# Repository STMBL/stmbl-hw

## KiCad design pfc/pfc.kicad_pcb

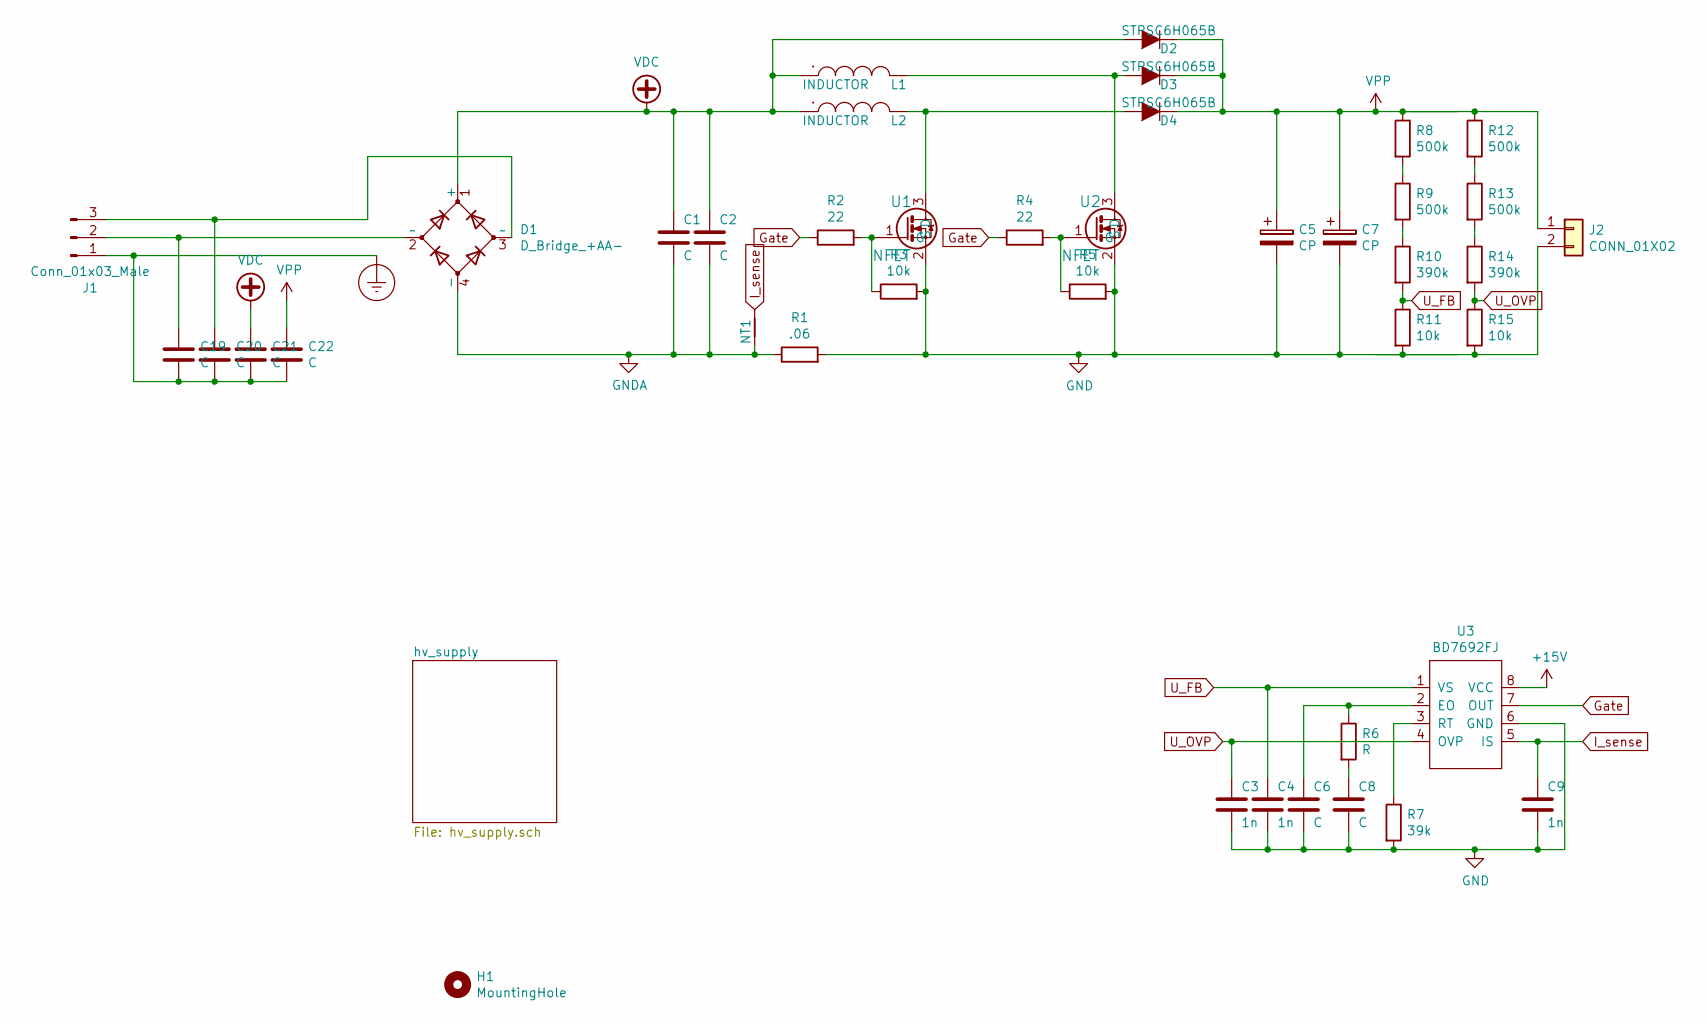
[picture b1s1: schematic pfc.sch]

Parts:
C1, C2: C; C_1812
C3, C4, C9: 1n; C_0603
C5, C7: CP; CP_Radial_D18.0mm_P7.50mm
C6, C8: C; C_0603
C19, C20, C21, C22: C; C_1808
D1: D_Bridge_+AA-; dfb_bridge
D2, D3, D4: STPSC6H065B; TO-252-2_STSiC
H1: MountingHole; MountingHole_3mm
J1: Conn_01x03_Male; RM7.62_1x3
J2: CONN_01X02; RM7.62_1x2
L1, L2: INDUCTOR; PQ2617BHA
NT1: Net-Tie_2; NetTie-2_SMD_Pad0.5mm
R1: .06; R_2512_BIG
R2, R4: 22; R_0805
R3, R5, R11, R15: 10k; R_0805
R6: R; C_0603
R7: 39k; C_0603
R8, R9, R12, R13: 500k; R_0805
R10, R14: 390k; R_0805
U1, U2: NFET; TO-220-3_Horizontal_TabDown_small_pads
U3: BD7692FJ; SOIC-8-N

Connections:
+15V: U3.8 (VCC); also elsewhere on the board
Earth_Protective: C19.2, C20.2, C21.2, C22.2, J1.1
GND: C3.2, C4.2, C5.2, C6.2, C7.2, C8.2, C9.2, J2.2, R1.2, R3.2, R5.2, R7.2, R11.2, R15.2, U1.2 (S), U2.2 (S), U3.6 (GND); also elsewhere on the board
GNDA: C1.2, C2.2, D1.4 (-), NT1.1, R1.1
Gate: R2.1, R4.1, U3.7 (OUT)
I_sense: C9.1, NT1.2, U3.5 (IS)
unnamed: C6.1, R6.1, U3.2 (EO)
unnamed: C8.1, R6.2
unnamed: C19.1, D1.2 (~~), J1.2
unnamed: C20.1, D1.3 (~~), J1.3
unnamed: D3.2 (A), L1.2, U2.3 (D)
unnamed: D4.2 (A), L2.2, U1.3 (D)
unnamed: R2.2, R3.1, U1.1 (G)
unnamed: R4.2, R5.1, U2.1 (G)
unnamed: R7.1, U3.3 (RT)
unnamed: R8.2, R9.1
unnamed: R9.2, R10.1
unnamed: R12.2, R13.1
unnamed: R13.2, R14.1
U_FB: C4.1, R10.2, R11.1, U3.1 (VS)
U_OVP: C3.1, R14.2, R15.1, U3.4 (OVP)
VDC: C1.1, C2.1, C21.1, D1.1 (+), D2.2 (A), L1.1, L2.1
VPP: C5.1, C7.1, C22.1, D2.1 (K), D3.1 (K), D4.1 (K), J2.1, R8.1, R12.1; also elsewhere on the board

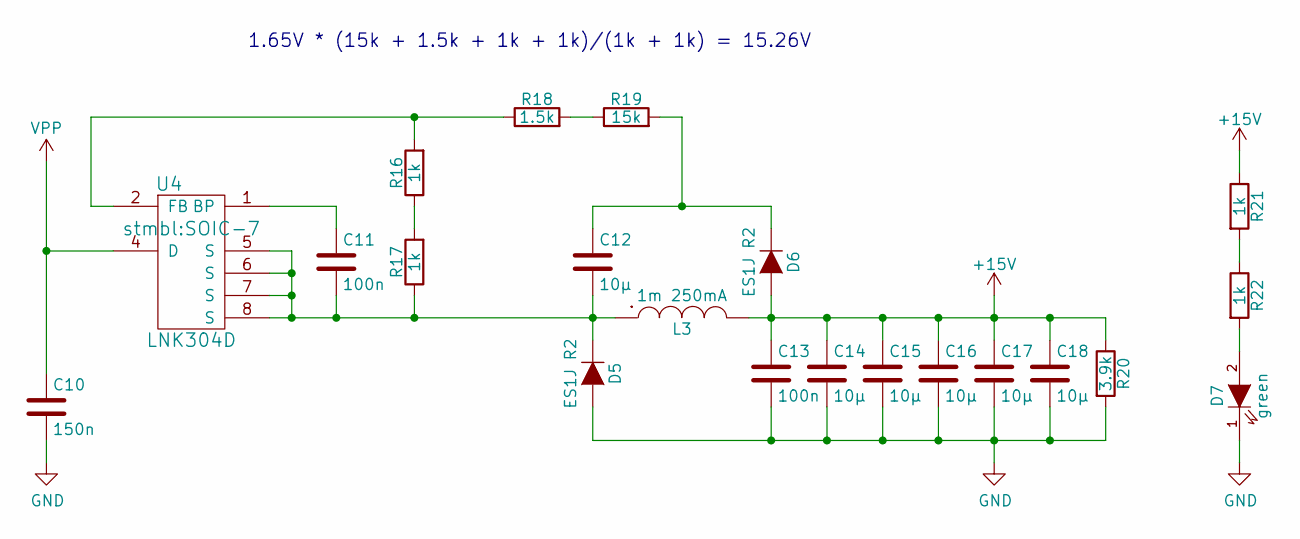
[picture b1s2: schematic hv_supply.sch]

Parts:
C10: 150n; C_1808; Voltage 500V; Tolerance X7R
C11, C13: 100n; C_0603; Voltage 50V; Tolerance X5R
C12, C14, C15, C16, C17, C18: 10µ; C_0805; Voltage 25V; Tolerance X5R
D5, D6: ES1J R2; SMA_Standard
D7: green; LED-0805-SIDE
L3: 1m 250mA; NPI31W
R16, R17, R21, R22: 1k; R_0603; Tolerance 1%
R18: 1.5k; R_0603; Tolerance 1%
R19: 15k; R_0603; Tolerance 1%
R20: 3.9k; R_0603; Tolerance 1%
U4: LNK304D; SOIC-7

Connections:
+15V: C13.1, C14.1, C15.1, C16.1, C17.1, C18.1, D6.2 (A), L3.2, R20.1, R21.1; also elsewhere on the board
GND: C10.2, C13.2, C14.2, C15.2, C16.2, C17.2, C18.2, D5.2 (A), D7.1 (K), R20.2; also elsewhere on the board
unnamed: C11.1, U4.1 (BP)
unnamed: C11.2, C12.2, D5.1 (K), L3.1, R17.1, U4.5 (S), U4.6 (S), U4.7 (S), U4.8 (S)
unnamed: C12.1, D6.1 (K), R19.2
unnamed: D7.2 (A), R22.2
unnamed: R16.1, R17.2
unnamed: R16.2, R18.1, U4.2 (FB)
unnamed: R18.2, R19.1
unnamed: R21.2, R22.1
VPP: C10.1, U4.4 (D); also elsewhere on the board

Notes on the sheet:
1.65V * (15k + 1.5k + 1k + 1k)/(1k + 1k) = 15.26V

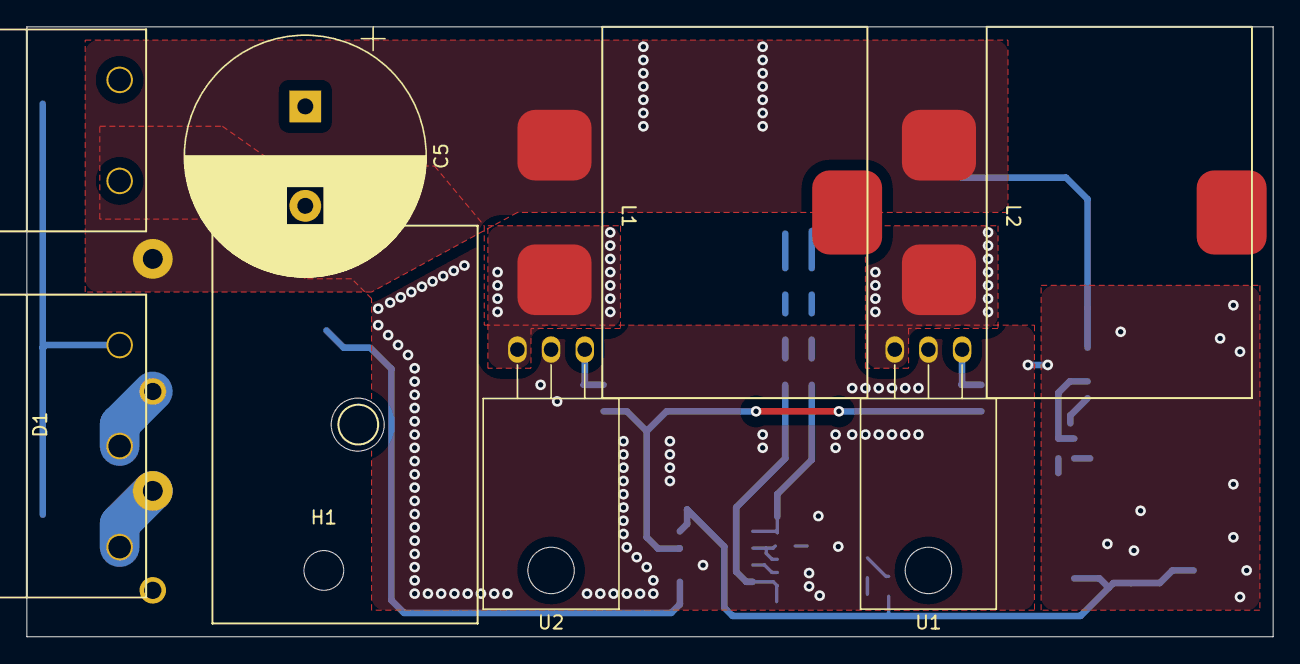
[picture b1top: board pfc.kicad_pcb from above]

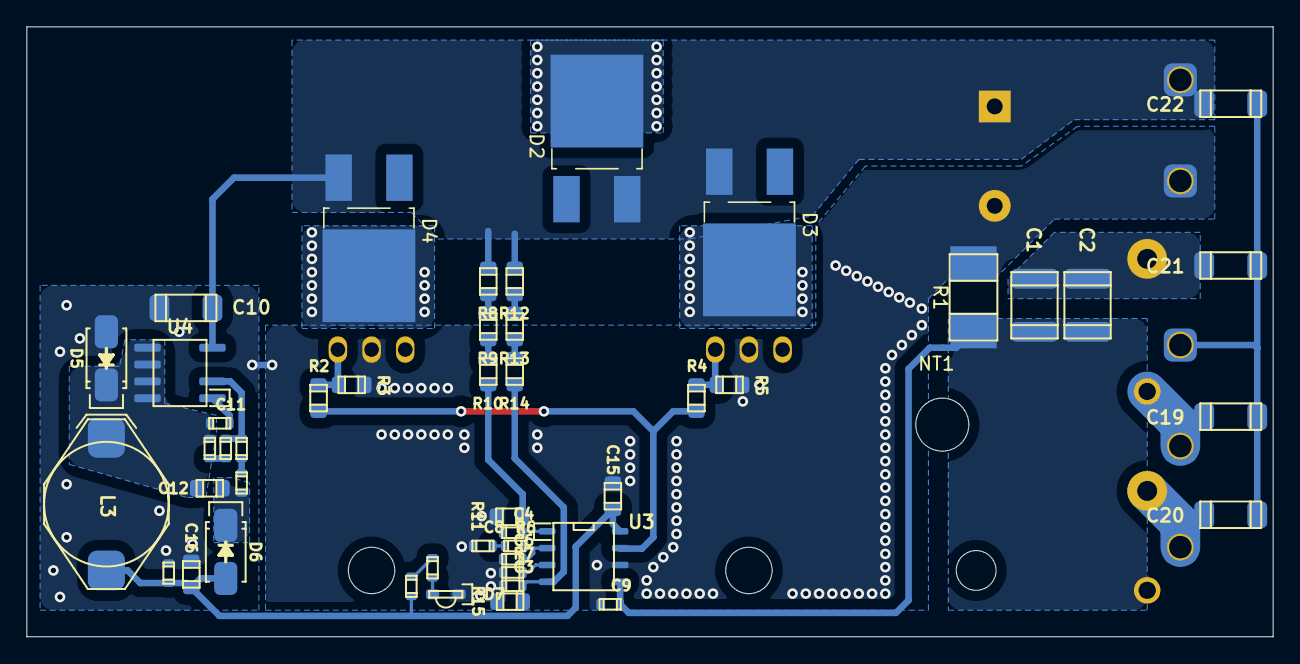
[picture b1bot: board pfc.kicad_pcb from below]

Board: 2 copper layers, 94.0 x 46.0 mm, 57 parts (48 on the bottom side), 31 nets.

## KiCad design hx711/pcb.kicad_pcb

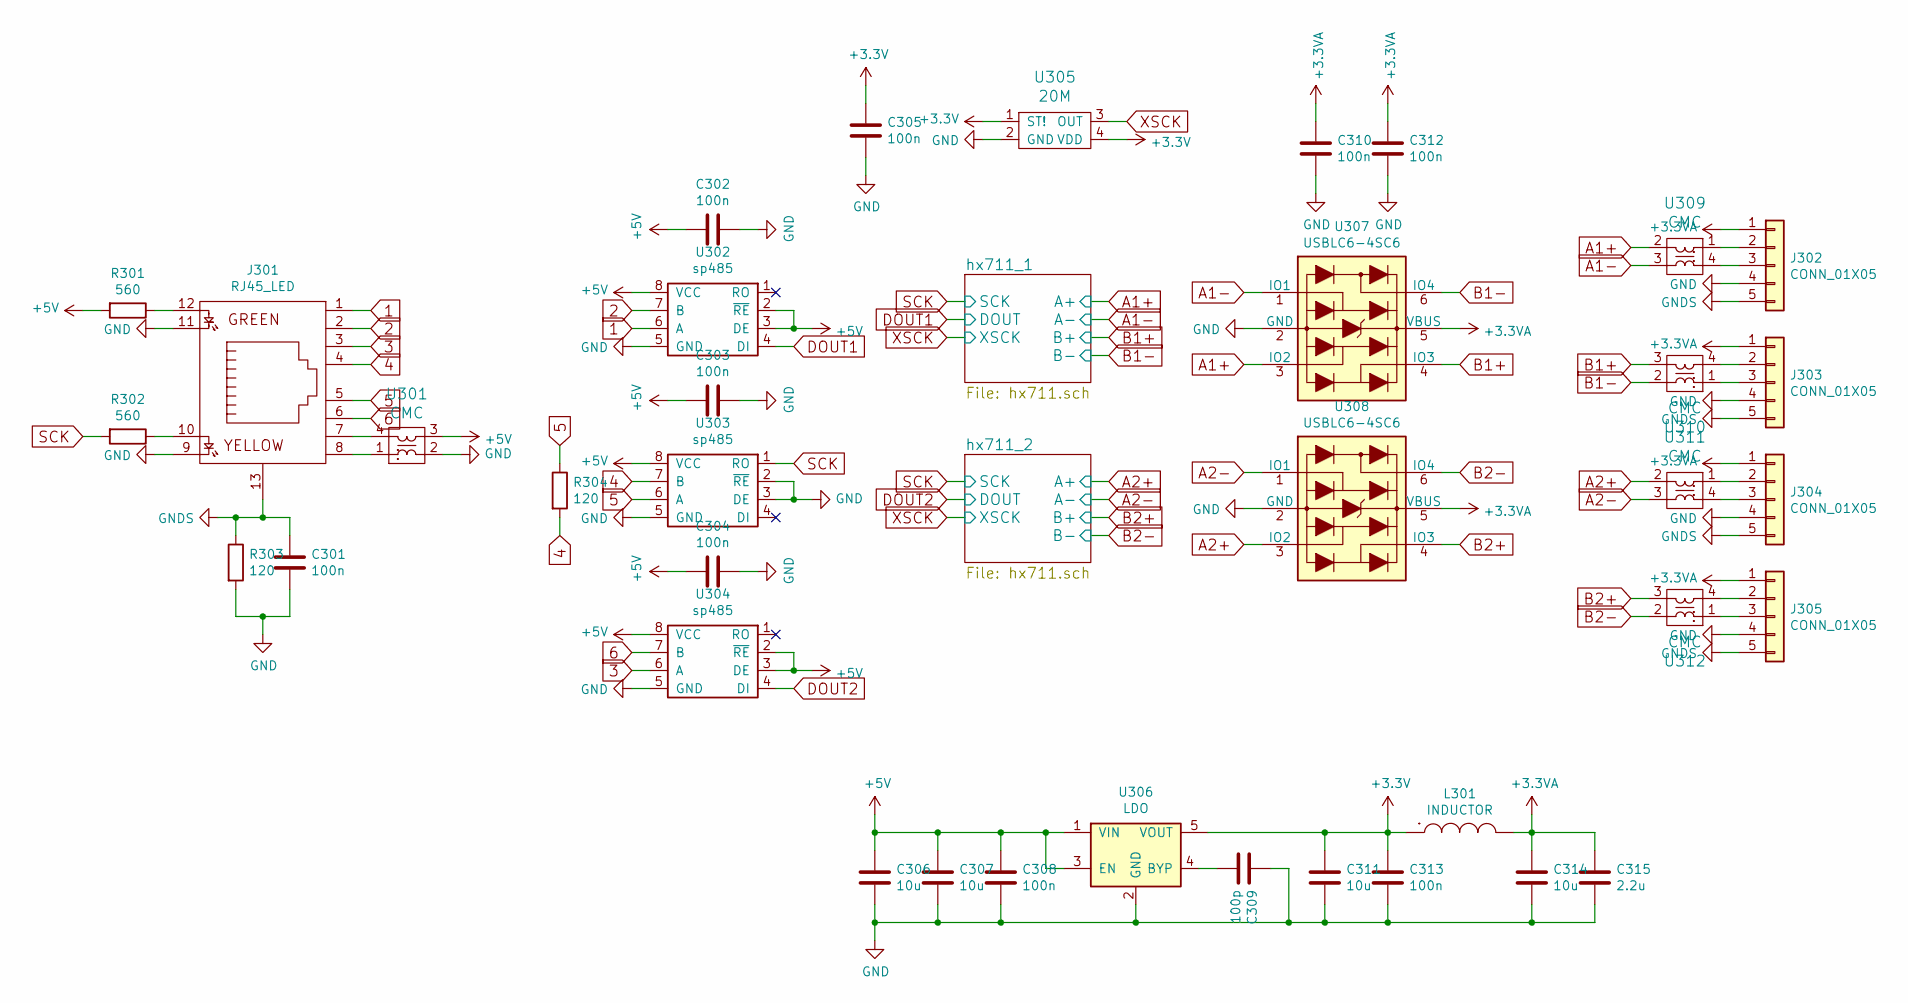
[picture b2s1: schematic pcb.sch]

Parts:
C301, C302, C303, C304, C305, C308, C310, C312, C313: 100n; C_0603; LCSC C14663
C306, C307, C311, C314: 10u; C_0805; LCSC C15850
C309: 100p; C_0603; LCSC C14858
C315: 2.2u; C_0603; LCSC C23630
J301: RJ45_LED
J302, J303, J304, J305: CONN_01X05; Pin_Header_RM2.54_1x5_UP
L301: INDUCTOR; R_0603; LCSC C73100
R301, R302: 560; C_0603; LCSC C23204
R303, R304: 120; R_0603; LCSC C22787
U301, U309, U310, U311, U312: CMC; CMC_0805; LCSC C80529
U302, U303, U304: sp485; SOIC-8-N; LCSC C6855
U305: 20M; Oscillator_SMD_0603_4Pads; LCSC C32529
U306: LDO; SOT-23-5; LCSC C9055
U307, U308: USBLC6-4SC6; SOT-23-6; LCSC C111212

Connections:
1: J301.1, U302.6 (A)
2: J301.2, U302.7 (B)
3: J301.3, U304.6 (A)
4: J301.4, R304.2, U303.7 (B)
5: J301.5, R304.1, U303.6 (A)
6: J301.6, U304.7 (B)
+3.3VA: C310.1, C312.1, C314.1, C315.1, J302.1, J303.1, J304.1, J305.1, L301.2, U307.5 (VBUS), U308.5 (VBUS); also elsewhere on the board
+3V3: C305.1, C311.1, C313.1, L301.1, U305.1 (ST!), U305.4 (VDD), U306.5 (VOUT)
+5V: C302.1, C303.1, C304.1, C306.1, C307.1, C308.1, R301.2, U301.3, U302.2 (~RE~), U302.3 (DE), U302.8 (VCC), U303.8 (VCC), U304.2 (~RE~), U304.3 (DE), U304.8 (VCC), U306.1 (VIN), U306.3 (EN); also elsewhere on the board
A1+: U307.3 (IO2), U309.2; also elsewhere on the board
A1-: U307.1 (IO1), U309.3; also elsewhere on the board
A2+: U308.3 (IO2), U311.2; also elsewhere on the board
A2-: U308.1 (IO1), U311.3; also elsewhere on the board
B1+: U307.4 (IO3), U310.3; also elsewhere on the board
B1-: U307.6 (IO4), U310.2; also elsewhere on the board
B2+: U308.4 (IO3), U312.3; also elsewhere on the board
B2-: U308.6 (IO4), U312.2; also elsewhere on the board
DOUT1: U302.4 (DI); also elsewhere on the board
DOUT2: U304.4 (DI); also elsewhere on the board
GND: C301.2, C302.2, C303.2, C304.2, C305.2, C306.2, C307.2, C308.2, C309.1, C310.2, C311.2, C312.2, C313.2, C314.2, C315.2, J301.9, J301.11, J302.4, J303.4, J304.4, J305.4, R303.2, U301.2, U302.5 (GND), U303.2 (~RE~), U303.3 (DE), U303.5 (GND), U304.5 (GND), U305.2 (GND), U306.2 (GND), U307.2 (GND), U308.2 (GND); also elsewhere on the board
GNDS: C301.1, J301.13, J302.5, J303.5, J304.5, J305.5, R303.1
unnamed: C309.2, U306.4 (BYP)
unnamed: J301.7, U301.4
unnamed: J301.8, U301.1
unnamed: J301.10, R302.1
unnamed: J301.12, R301.1
unnamed: J302.2, U309.1
unnamed: J302.3, U309.4
unnamed: J303.2, U310.4
unnamed: J303.3, U310.1
unnamed: J304.2, U311.1
unnamed: J304.3, U311.4
unnamed: J305.2, U312.4
unnamed: J305.3, U312.1
SCK: R302.2, U303.1 (RO); also elsewhere on the board
XSCK: U305.3 (OUT); also elsewhere on the board

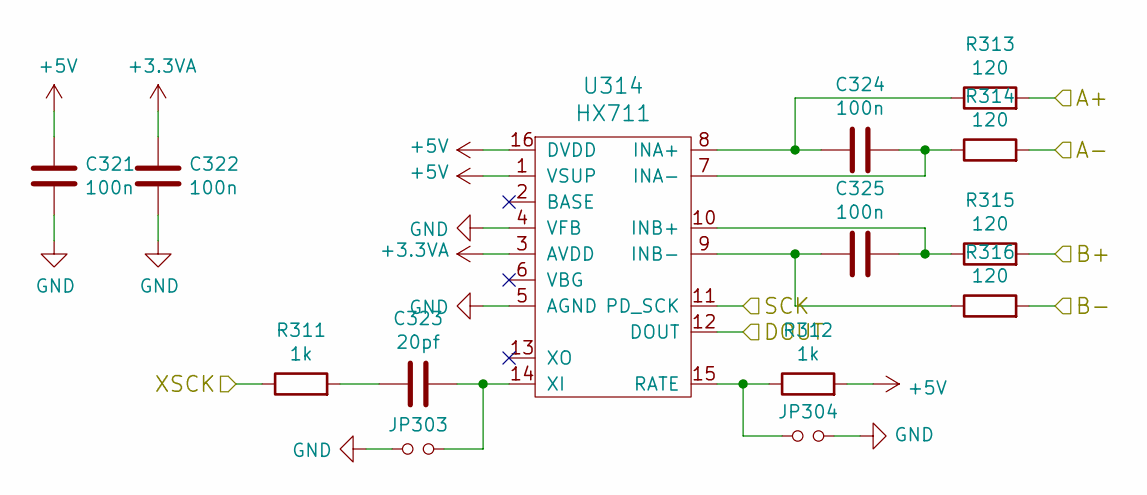
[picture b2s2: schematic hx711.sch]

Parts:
C316, C317, C319, C320: 100n; C_0603; LCSC C14663
C318: 20pf; C_0603; LCSC C1648
JP301, JP302: Jumper_NO_Small; 0603_jumper
R305, R306: 1k; R_0603; LCSC C21190
R307, R308, R309, R310: 120; R_0603; LCSC C22787
U313: HX711; SOIC-16; LCSC C43656

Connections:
+3.3VA: C317.2, U313.3 (AVDD); also elsewhere on the board
+5V: C316.2, R306.2, U313.1 (VSUP), U313.16 (DVDD); also elsewhere on the board
A2+: R307.2; also elsewhere on the board
A2-: R308.2; also elsewhere on the board
B2+: R309.2; also elsewhere on the board
B2-: R310.2; also elsewhere on the board
DOUT2: U313.12 (DOUT); also elsewhere on the board
GND: C316.1, C317.1, JP301.1, JP302.2, U313.4 (VFB), U313.5 (AGND); also elsewhere on the board
unnamed: C318.1, R305.2
unnamed: C318.2, JP301.2, U313.14 (XI)
unnamed: C319.1, R308.1, U313.7 (INA-)
unnamed: C319.2, R307.1, U313.8 (INA+)
unnamed: C320.1, R309.1, U313.10 (INB+)
unnamed: C320.2, R310.1, U313.9 (INB-)
unnamed: JP302.1, R306.1, U313.15 (RATE)
SCK: U313.11 (PD_SCK); also elsewhere on the board
XSCK: R305.1; also elsewhere on the board

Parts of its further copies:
C321, C322, C324, C325: 100n; C_0603; LCSC C14663
C323: 20pf; C_0603; LCSC C1648
JP303, JP304: Jumper_NO_Small; 0603_jumper
R311, R312: 1k; R_0603; LCSC C21190
R313, R314, R315, R316: 120; R_0603; LCSC C22787
U314: HX711; SOIC-16; LCSC C43656

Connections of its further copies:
+3.3VA: C322.2, U314.3 (AVDD); also elsewhere on the board
+5V: C321.2, R312.2, U314.1 (VSUP), U314.16 (DVDD); also elsewhere on the board
A1+: R313.2; also elsewhere on the board
A1-: R314.2; also elsewhere on the board
B1+: R315.2; also elsewhere on the board
B1-: R316.2; also elsewhere on the board
DOUT1: U314.12 (DOUT); also elsewhere on the board
GND: C321.1, C322.1, JP303.1, JP304.2, U314.4 (VFB), U314.5 (AGND); also elsewhere on the board
unnamed: C323.1, R311.2
unnamed: C323.2, JP303.2, U314.14 (XI)
unnamed: C324.1, R314.1, U314.7 (INA-)
unnamed: C324.2, R313.1, U314.8 (INA+)
unnamed: C325.1, R315.1, U314.10 (INB+)
unnamed: C325.2, R316.1, U314.9 (INB-)
unnamed: JP304.1, R312.1, U314.15 (RATE)
SCK: U314.11 (PD_SCK); also elsewhere on the board
XSCK: R311.1; also elsewhere on the board

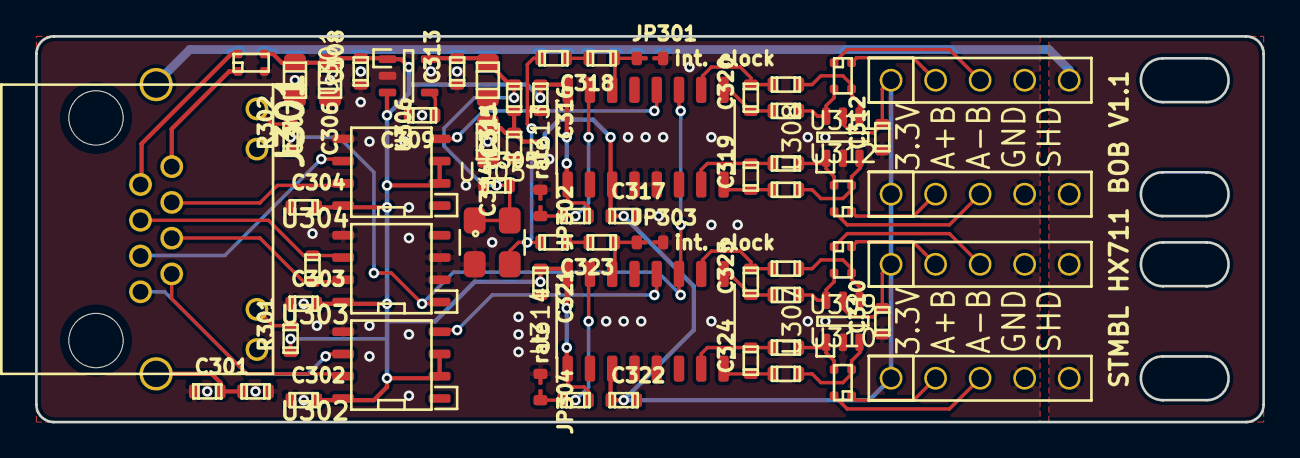
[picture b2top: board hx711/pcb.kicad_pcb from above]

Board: 4 copper layers, 70.0 x 22.0 mm, 65 parts (0 on the bottom side), 50 nets.

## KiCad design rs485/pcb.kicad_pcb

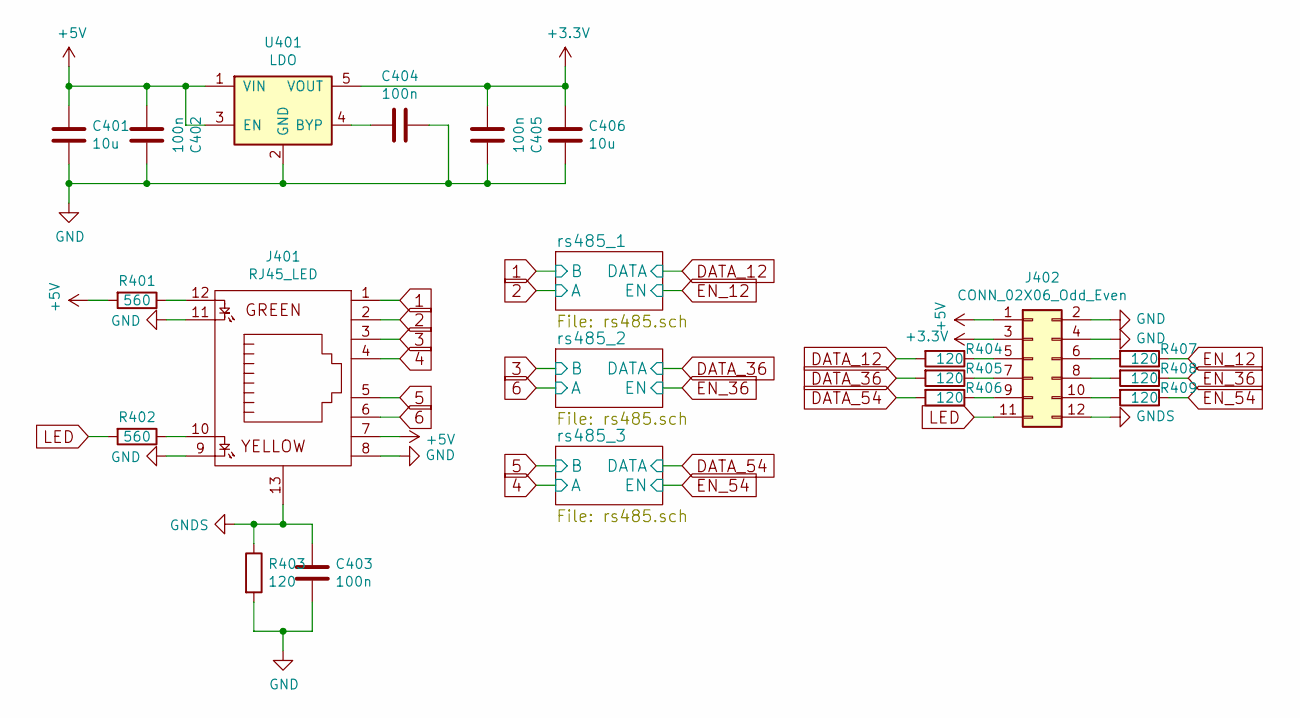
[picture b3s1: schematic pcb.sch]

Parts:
C401, C406: 10u; C_0805; LCSC C15850
C402, C403, C404, C405: 100n; C_0603; LCSC C14663
J401: RJ45_LED
J402: CONN_02X06_Odd_Even; Pin_Header_RM2.54_2x6_UP
R401, R402: 560; C_0603; LCSC C23204
R403, R404, R405, R406, R407, R408, R409: 120; C_0603; LCSC C22787
U401: LDO; SOT-23-5; LCSC C9055

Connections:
1: J401.1; also elsewhere on the board
2: J401.2; also elsewhere on the board
3: J401.3; also elsewhere on the board
4: J401.4; also elsewhere on the board
5: J401.5; also elsewhere on the board
6: J401.6; also elsewhere on the board
+3V3: C405.1, C406.1, J402.3, U401.5 (VOUT)
+5V: C401.1, C402.1, J401.7, J402.1, R401.2, U401.1 (VIN), U401.3 (EN); also elsewhere on the board
DATA_12: R404.2; also elsewhere on the board
DATA_36: R405.2; also elsewhere on the board
DATA_54: R406.2; also elsewhere on the board
EN_12: R407.1; also elsewhere on the board
EN_36: R408.1; also elsewhere on the board
EN_54: R409.1; also elsewhere on the board
GND: C401.2, C402.2, C403.2, C404.2, C405.2, C406.2, J401.8, J401.9, J401.11, J402.2, J402.4, R403.2, U401.2 (GND); also elsewhere on the board
GNDS: C403.1, J401.13, J402.12, R403.1
LED: J402.11, R402.2
unnamed: C404.1, U401.4 (BYP)
unnamed: J401.10, R402.1
unnamed: J401.12, R401.1
unnamed: J402.5, R404.1
unnamed: J402.6, R407.2
unnamed: J402.7, R405.1
unnamed: J402.8, R408.2
unnamed: J402.9, R406.1
unnamed: J402.10, R409.2

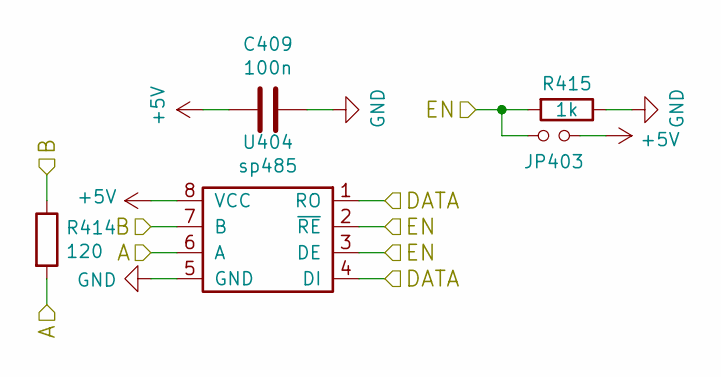
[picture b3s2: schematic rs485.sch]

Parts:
C407: 100n; C_0603; LCSC C14663
JP401: Jumper_NO_Small; 0603_jumper
R410: 120; C_0603; LCSC C22787
R411: 1k; R_0603; LCSC C21190
U402: sp485; SOIC-8-N; LCSC C6855

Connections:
1: R410.1, U402.7 (B); also elsewhere on the board
2: R410.2, U402.6 (A); also elsewhere on the board
+5V: C407.1, JP401.2, U402.8 (VCC); also elsewhere on the board
DATA_12: U402.1 (RO), U402.4 (DI); also elsewhere on the board
EN_12: JP401.1, R411.2, U402.2 (~RE~), U402.3 (DE); also elsewhere on the board
GND: C407.2, R411.1, U402.5 (GND); also elsewhere on the board

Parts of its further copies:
C408, C409: 100n; C_0603; LCSC C14663
JP402, JP403: Jumper_NO_Small; 0603_jumper
R412, R414: 120; C_0603; LCSC C22787
R413, R415: 1k; R_0603; LCSC C21190
U403, U404: sp485; SOIC-8-N; LCSC C6855

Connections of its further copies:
3: R412.1, U403.7 (B); also elsewhere on the board
4: R414.2, U404.6 (A); also elsewhere on the board
5: R414.1, U404.7 (B); also elsewhere on the board
6: R412.2, U403.6 (A); also elsewhere on the board
+5V: C408.1, C409.1, JP402.2, JP403.2, U403.8 (VCC), U404.8 (VCC); also elsewhere on the board
DATA_36: U403.1 (RO), U403.4 (DI); also elsewhere on the board
DATA_54: U404.1 (RO), U404.4 (DI); also elsewhere on the board
EN_36: JP402.1, R413.2, U403.2 (~RE~), U403.3 (DE); also elsewhere on the board
EN_54: JP403.1, R415.2, U404.2 (~RE~), U404.3 (DE); also elsewhere on the board
GND: C408.2, C409.2, R413.1, R415.1, U403.5 (GND), U404.5 (GND); also elsewhere on the board

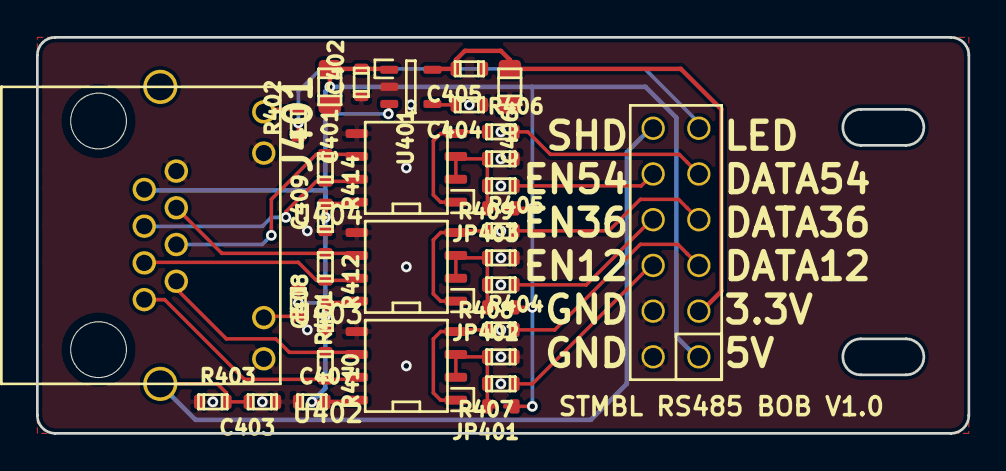
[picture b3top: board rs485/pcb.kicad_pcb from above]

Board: 4 copper layers, 51.8 x 22.0 mm, 33 parts (0 on the bottom side), 26 nets.

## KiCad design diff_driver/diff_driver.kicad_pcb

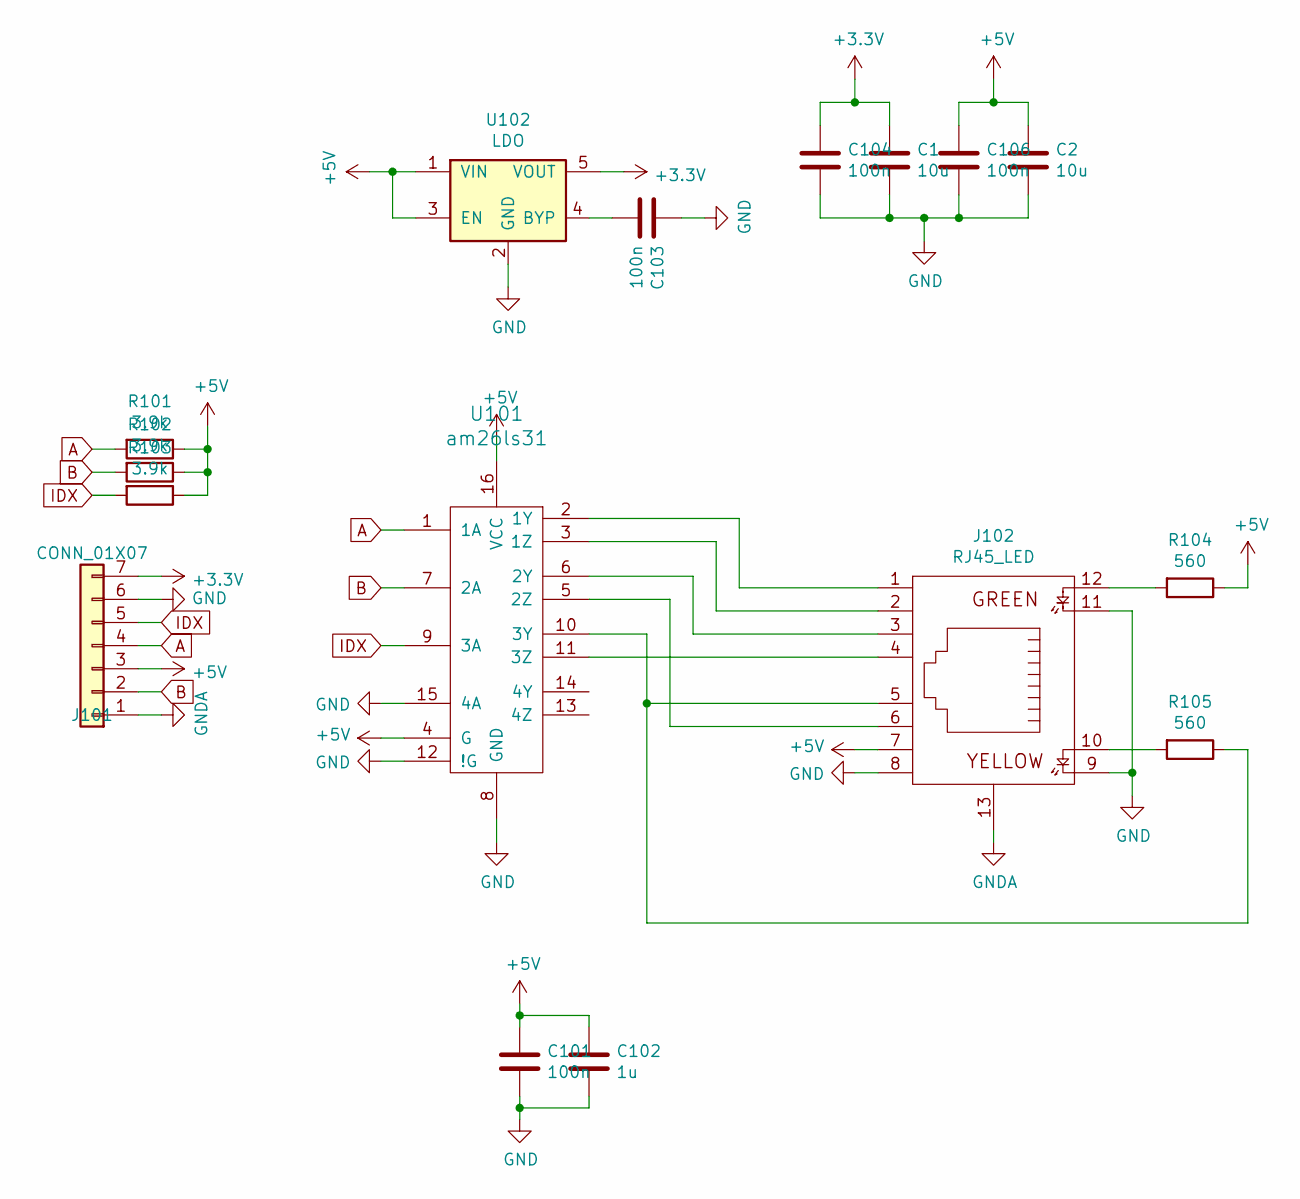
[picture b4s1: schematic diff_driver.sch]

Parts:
C1, C2: 10u; C_0805; LCSC C15850
C101, C103, C104, C106: 100n; C_0603; LCSC C14663
C102: 1u; C_0603; LCSC C15849
J101: CONN_01X07; Pin_Header_RM2.54_1x7_UP
J102: RJ45_LED
R101, R102, R103: 3.9k; R_0603; LCSC C23018
R104, R105: 560; R_0603; LCSC C23204
U101: am26ls31; SOIC-16; LCSC C6179
U102: LDO; SOT-23-5; LCSC C9055

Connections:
+3V3: C1.1, C104.1, J101.7, U102.5 (VOUT)
+5V: C2.1, C101.1, C102.1, C106.1, J101.3, J102.7, R101.1, R102.1, R103.1, R104.1, U101.4 (G), U101.16 (VCC), U102.1 (VIN), U102.3 (EN)
A: J101.4, R101.2, U101.1 (1A)
B: J101.2, R102.2, U101.7 (2A)
GND: C1.2, C2.2, C101.2, C102.2, C103.1, C104.2, C106.2, J101.6, J102.8, J102.9, J102.11, U101.8 (GND), U101.12 (!G), U101.15 (4A), U102.2 (GND)
GNDA: J101.1, J102.13
IDX: J101.5, R103.2, U101.9 (3A)
unnamed: C103.2, U102.4 (BYP)
unnamed: J102.1, U101.2 (1Y)
unnamed: J102.2, U101.3 (1Z)
unnamed: J102.3, U101.6 (2Y)
unnamed: J102.4, U101.11 (3Z)
unnamed: J102.5, R105.1, U101.10 (3Y)
unnamed: J102.6, U101.5 (2Z)
unnamed: J102.10, R105.2
unnamed: J102.12, R104.2

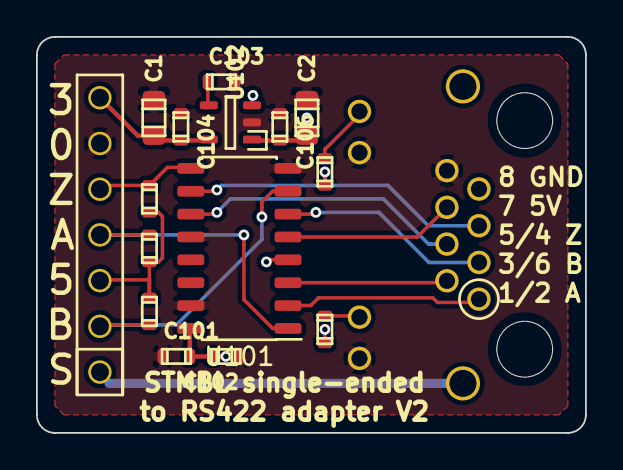
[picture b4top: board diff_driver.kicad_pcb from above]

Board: 2 copper layers, 30.5 x 22.0 mm, 16 parts (1 on the bottom side), 16 nets.

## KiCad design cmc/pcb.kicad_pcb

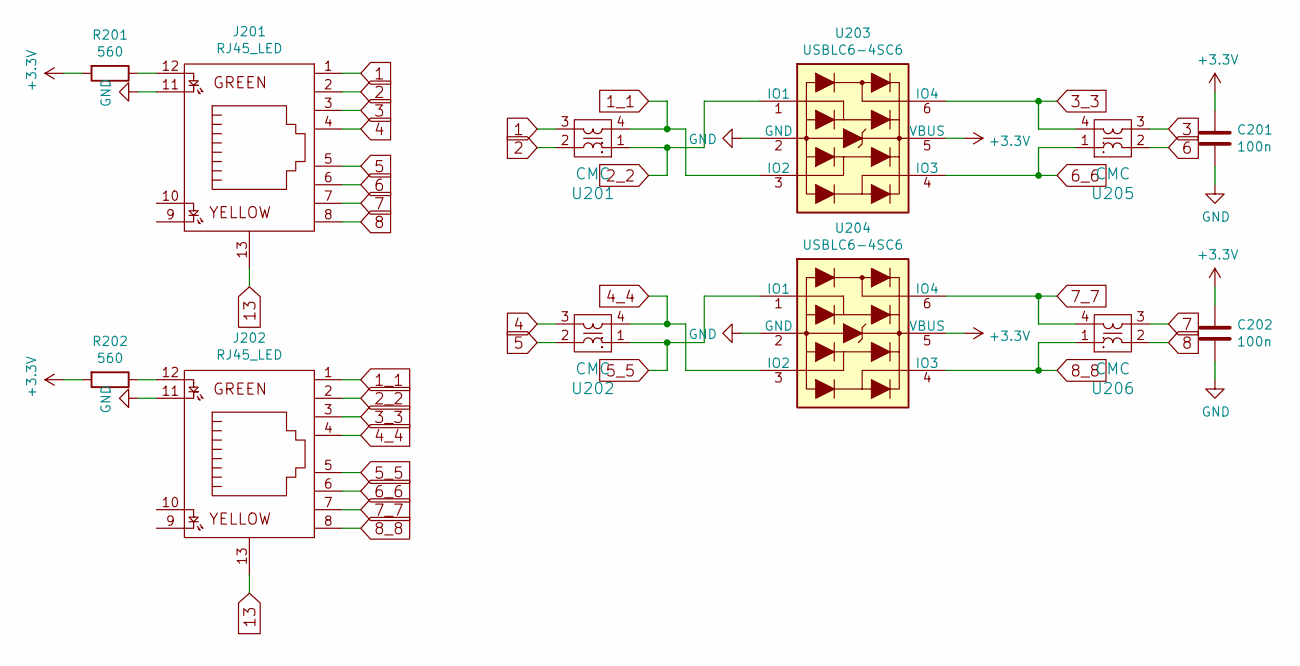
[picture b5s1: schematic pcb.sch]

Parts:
C201, C202: 100n; C_0603; LCSC C14663
J201, J202: RJ45_LED
R201, R202: 560; R_0603; LCSC C23204
U201, U202, U205, U206: CMC; CMC_0805; LCSC C80529
U203, U204: USBLC6-4SC6; SOT-23-6; LCSC C111212

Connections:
1: J201.1, U201.3
1_1: J202.1, U201.4, U203.3 (IO2)
2: J201.2, U201.2
2_2: J202.2, U201.1, U203.1 (IO1)
3: J201.3, U205.3
3_3: J202.3, U203.6 (IO4), U205.4
4: J201.4, U202.3
4_4: J202.4, U202.4, U204.3 (IO2)
5: J201.5, U202.2
5_5: J202.5, U202.1, U204.1 (IO1)
6: J201.6, U205.2
6_6: J202.6, U203.4 (IO3), U205.1
7: J201.7, U206.3
7_7: J202.7, U204.6 (IO4), U206.4
8: J201.8, U206.2
8_8: J202.8, U204.4 (IO3), U206.1
13: J201.13, J202.13
+3V3: C201.1, C202.1, R201.2, R202.2, U203.5 (VBUS), U204.5 (VBUS)
GND: C201.2, C202.2, J201.11, J202.11, U203.2 (GND), U204.2 (GND)
unnamed: J201.12, R201.1
unnamed: J202.12, R202.1

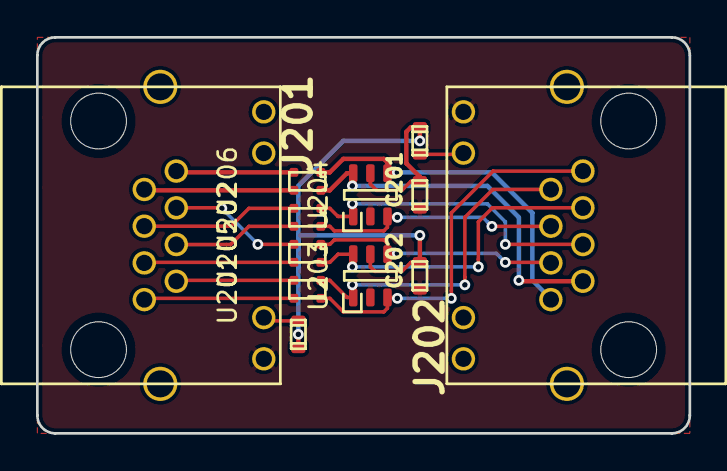
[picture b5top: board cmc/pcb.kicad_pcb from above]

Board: 4 copper layers, 36.2 x 22.0 mm, 12 parts (0 on the bottom side), 21 nets.

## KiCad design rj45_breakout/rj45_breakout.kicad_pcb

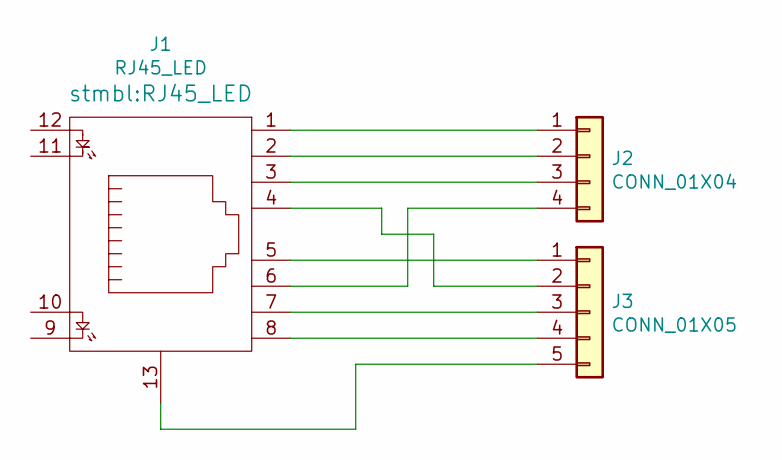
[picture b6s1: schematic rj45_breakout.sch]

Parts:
J1: RJ45_LED
J2: CONN_01X04; RM3.5_1x4_UP
J3: CONN_01X05; RM3.5_1x5_UP

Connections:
unnamed: J1.1, J2.1
unnamed: J1.2, J2.2
unnamed: J1.3, J2.3
unnamed: J1.4, J3.2
unnamed: J1.5, J3.1
unnamed: J1.6, J2.4
unnamed: J1.7, J3.3
unnamed: J1.8, J3.4
unnamed: J1.13, J3.5

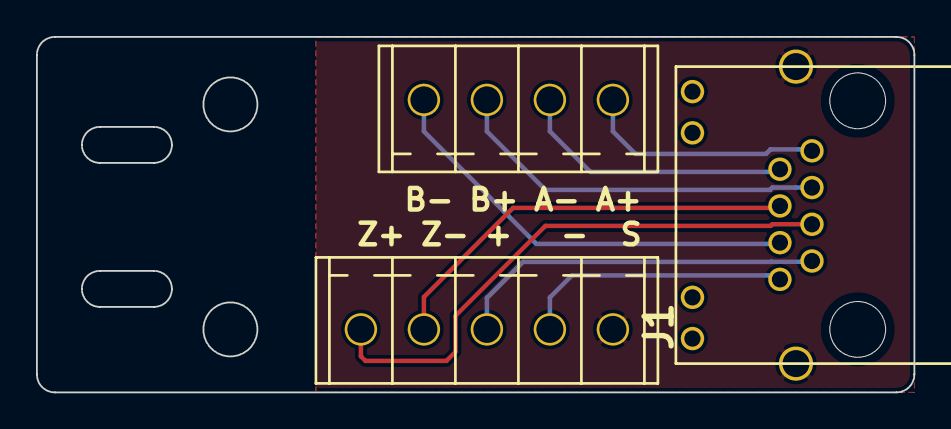
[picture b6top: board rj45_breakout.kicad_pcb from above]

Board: 2 copper layers, 48.8 x 19.8 mm, 3 parts (0 on the bottom side), 9 nets.
